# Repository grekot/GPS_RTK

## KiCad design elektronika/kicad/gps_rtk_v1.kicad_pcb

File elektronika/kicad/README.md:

# KiCad — schemat odbiornika GPS RTK (v1)

`gps_rtk_v1.kicad_sch` to **pełny schemat** z prawdziwymi symbolami KiCad i połączeniami
(po nazwach netów). Wygenerowany skryptem [gen/gen_schematic.py](gen/gen_schematic.py) z bibliotek
symboli KiCad 9, **zweryfikowany netlistą** i wyrenderowany do
[gps_rtk_v1.pdf](gps_rtk_v1.pdf) / [gps_rtk_v1.svg](gps_rtk_v1.svg).

## Zawartość schematu

Symbole: **U1** ESP32-WROOM-32; złącza modułów: **J1** GNSS LC29HEA, **J2** OLED SSD1306,
**J3** IMU BNO085 (v2, DNP), **J4** buck-boost 3V3, **J5** TP4056 USB-C; **BT1** ogniwo 18650;
dzielnik baterii **R1/R2** (100k); pull-upy I2C **R3/R4** (4k7); **R5**+**D1** LED statusu;
**SW1** przycisk; **C1/C2** bulk/odsprzęganie.

Nety (zweryfikowane netlistą): `+3V3, GND, VBAT, VBAT_SENSE, BATT_CELL, VBUS, GNSS_TX, GNSS_RX,
GNSS_PPS, GNSS_RST, SDA, SCL, LED_STAT, LED_A, BTN`. Zgodne z [../docs/05-pinout-firmware.md](../docs/05-pinout-firmware.md)
i [../docs/02-schemat-polaczen.md](../docs/02-schemat-polaczen.md).

> **Styl:** połączenia przez **etykiety netów po nazwie** (a nie rysowane przewody między częściami) —
> typowe i czytelne przy gęstych wyprowadzeniach MCU. Moduły jako złącza — w v1 to i tak gotowe
> płytki łączone przewodami. 24 nieużywane GPIO ESP32 zostają wolne (zapas).

## PCB — carrier `gps_rtk_v1.kicad_pcb`

**Płytka-baza (carrier) 100 × 78 mm**: wszystkie elementy aktywne to **gotowe moduły wpinane
w gniazda żeńskie** (łącznie z ESP32 jako devkit). Wygenerowana [gen/gen_pcb.py](gen/gen_pcb.py)
(pcbnew — Python KiCada). Podgląd: **[render 3D PNG](gps_rtk_v1_pcb.png)**, [2D SVG](gps_rtk_v1_pcb.svg).

Gniazda **PinSocket 2.54 mm**: **U1L+U1R** = ESP32 **DOIT DevKit V1 (30-pin)**, 2× **1×15**;
**J1** GNSS LC29HEA (1×06), **J2** OLED (1×04), **J3** IMU v2 (1×04), **J4** buck-boost (1×04),
**J5** TP4056 (1×06), **BT1** ogniwo (1×02). Na carrierze (SMD/THT): dzielnik **R1/R2**,
pull-upy I2C **R3/R4**, **R5+D1** LED, **C1/C2** bulk/odsprzęg., **SW1** przycisk.

**ESP32 jako devkit:** 3.3 V wchodzi na pin **3V3**; **EN i VIN(5V) wolne** — devkit ma własny
auto-reset i LDO (podpięcie EN do 3V3 zablokowałoby programowanie!). (Schemat pokazuje ESP32 jako
symbol WROOM — logicznie równoważny; na płytce to gniazdo devkitu.)

> **Zasilanie v1 = powerbank przez USB devkitu** (decyzja użytkownika). W tym trybie **nie montuj**
> modułów zasilania: buck-boost (J4), TP4056 (J5), ogniwo (BT1) ani dzielnika baterii (R1/R2) — szynę
> **+3V3** napędza wtedy AMS1117 devkitu. Sekcja bateryjna zostaje na płytce jako **opcja terenowa/v2**.

### Pinout ESP32 użyty na płytce — ZWERYFIKUJ z nadrukiem swojej płytki!

Kolejność fizyczna góra→dół (DOIT DevKit V1 30-pin). **Pogrubione = podłączone (mają net):**

| U1L (lewa) | net | · | U1R (prawa) | net |
|---|---|---|---|---|
| 1 EN | — | · | 1 3V3 | **+3V3** |
| 2 IO36 | — | · | 2 GND | **GND** |
| 3 IO39 | — | · | 3 IO15 | — |
| **4 IO34** | **VBAT_SENSE** | · | **4 IO2** | **LED_STAT** |
| **5 IO35** | **GNSS_PPS** | · | **5 IO4** | **GNSS_RST** |
| 6 IO32 | — | · | **6 IO16** | **GNSS_TX** |
| 7 IO33 | — | · | **7 IO17** | **GNSS_RX** |
| 8 IO25 | — | · | 8 IO5 | — |
| 9 IO26 | — | · | 9 IO18 | — |
| **10 IO27** | **BTN** | · | 10 IO19 | — |
| 11 IO14 | — | · | **11 IO21** | **SDA** |
| 12 IO12 | — | · | 12 IO3 | — |
| 13 IO13 | — | · | 13 IO1 | — |
| **14 GND** | **GND** | · | **14 IO22** | **SCL** |
| 15 VIN | — | · | 15 IO23 | — |

**Stan: rozmieszczona + onetowana, NIETRASOWANA** (ratsnest). DRC: **0 naruszeń**, 0 błędów
footprintów; **43 pady do połączenia = trasowanie**.

> ⚠️ **Zweryfikuj pod swój egzemplarz:** (1) **rozstaw rzędów** gniazd ESP32 — przyjąłem **22,86 mm**
> (stała `ESP_ROW_MM` w [gen/gen_pcb.py](gen/gen_pcb.py)); zmierz środek-do-środka rzędów i popraw.
> (2) **Pinout** wg tabeli wyżej — klony 30-pin bywają różne; jeśli się różni, popraw listy
> `ESP_L`/`ESP_R`. Rozmieszczenie zgrubne — dociągnij w GUI pod krótkie trasy.

## Weryfikacja (bez ERC — patrz niżej)

- ✅ **Netlista** (`kicad-cli sch export netlist`) — przeszła; każdy net ma dokładnie właściwe węzły
  (sprawdzone programowo: brak zlanych/rozjechanych netów).
- ✅ **Render** PDF/SVG (`kicad-cli sch export`) — bez błędów (10935 elementów rysunku).
- ⚠️ `kicad-cli sch erc` **crashuje** na tym pliku (quirk zgodności wyjścia generatora `kiutils`
  z silnikiem ERC w kicad-cli 9.0.9). Dlatego poprawność połączeń potwierdziłem **netlistą**, nie ERC.
  Po otwarciu i zapisaniu pliku w **GUI KiCada** (które normalizuje format) ERC powinien działać.

## Dalej (trasowanie + produkcja)

- **Trasowanie ścieżek** — jedyny brakujący krok: w GUI pcbnew, albo autorouterem **freerouting**
  (eksport `.dsn` → route → import `.ses`). Warto **wylać masę (GND pour)** — skróci ratsnest.
- Po trasowaniu: DRC w GUI, **gerbery** (`kicad-cli pcb export gerbers`), plik wierceń, BOM/CPL.
- Sekcja RF/bias anteny dla gołego modułu — patrz [../docs/02-schemat-polaczen.md](../docs/02-schemat-polaczen.md).

## Regeneracja / eksport

```powershell
$cli = "C:\TMP\kicad_portable\bin\kicad-cli.exe"   # lub kicad-cli z instalacji
py -3 gen\gen_schematic.py                          # wymaga: pip install kiutils
& $cli sch export pdf     --output gps_rtk_v1.pdf gps_rtk_v1.kicad_sch
& $cli sch export svg     --output .               gps_rtk_v1.kicad_sch
& $cli sch export netlist --output gps_rtk_v1.net  gps_rtk_v1.kicad_sch
# PCB (pcbnew — Python KiCada):
& "C:\TMP\kicad_portable\bin\python.exe" gen\gen_pcb.py
& $cli pcb drc    --output pcb.drc.rpt        gps_rtk_v1.kicad_pcb
& $cli pcb render --output gps_rtk_v1_pcb.png gps_rtk_v1.kicad_pcb
```

## Portable KiCad (rozpakowany w tej sesji)

Instalator rozpakowano 7-Zipem **bez instalacji i bez praw admina** do `C:\TMP\kicad_portable\`.
Działa GUI (`bin\kicad.exe`) i CLI (`bin\kicad-cli.exe`). Otwórz schemat:
`& "C:\TMP\kicad_portable\bin\kicad.exe" "...\elektronika\kicad\gps_rtk_v1.kicad_pro"`.
Folder można usunąć (~kilka GB) albo zachować jako przenośny KiCad.

## Instalacja KiCada na stałe (brak winget w systemie)

1. **Bezpośrednio:** <https://www.kicad.org/download/windows/> (KiCad 9/10).
2. **winget** (po doinstalowaniu „App Installer" z MS Store): `winget install -e --id KiCad.KiCad`.
3. **Chocolatey:** `choco install kicad`.

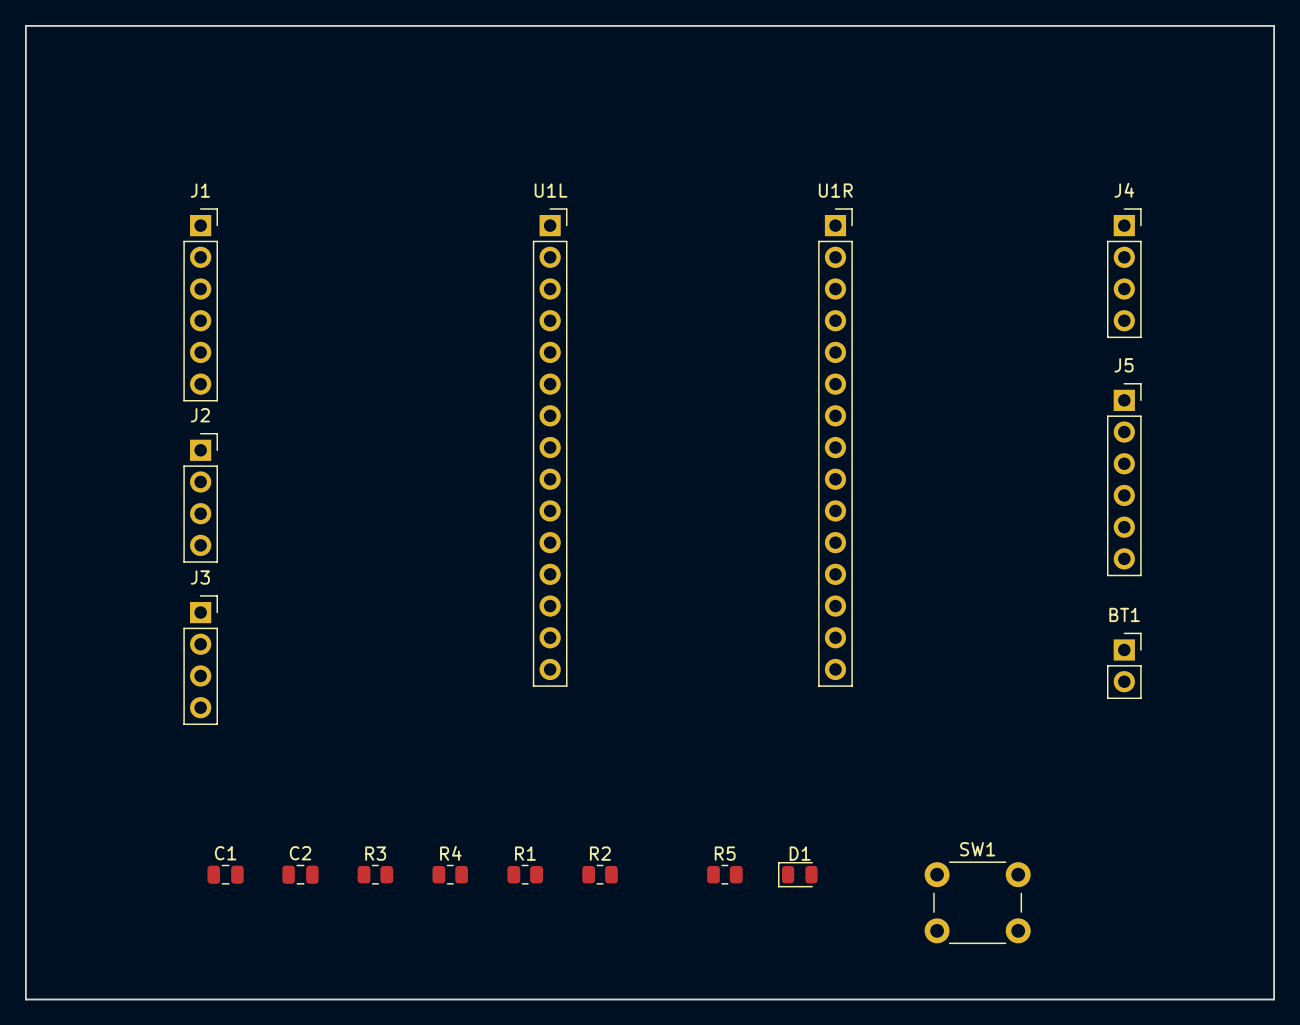
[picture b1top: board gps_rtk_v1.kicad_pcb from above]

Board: 2 copper layers, 100.0 x 78.0 mm, 17 parts (0 on the bottom side), 14 nets, no tracks yet.

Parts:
BT1: 18650 (przewody); PinSocket_1x02_P2.54mm_Vertical
C1: 100uF; C_0805_2012Metric
C2: 100nF; C_0805_2012Metric
D1: status; LED_0805_2012Metric
J1: GNSS LC29HEA (modul); PinSocket_1x06_P2.54mm_Vertical
J2: OLED SSD1306 (modul); PinSocket_1x04_P2.54mm_Vertical
J3: IMU BNO085 v2 (modul); PinSocket_1x04_P2.54mm_Vertical
J4: Buck-boost 3V3 (modul); PinSocket_1x04_P2.54mm_Vertical
J5: TP4056 USB-C (modul); PinSocket_1x06_P2.54mm_Vertical
R1, R2: 100k; R_0805_2012Metric
R3, R4: 4k7; R_0805_2012Metric
R5: 330; R_0805_2012Metric
SW1: user; SW_PUSH_6mm_H5mm
U1L: ESP32 DevKit V1 (L); PinSocket_1x15_P2.54mm_Vertical
U1R: ESP32 DevKit V1 (R); PinSocket_1x15_P2.54mm_Vertical

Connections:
+3V3: C1.1, C2.1, J1.1, J2.1, J3.1, J4.3, J4.4, R3.1, R4.1, U1R.1
BATT_CELL: BT1.1, J5.3
BTN: SW1.1, U1L.10
GND: BT1.2, C1.2, C2.2, D1.1, J1.2, J2.2, J3.2, J4.2, J5.2, J5.4, J5.6, R2.2, SW1.2, U1L.14, U1R.2
GNSS_PPS: J1.5, U1L.5
GNSS_RST: J1.6, U1R.5
GNSS_RX: J1.4, U1R.7
GNSS_TX: J1.3, U1R.6
LED_A: D1.2, R5.2
LED_STAT: R5.1, U1R.4
SCL: J2.3, J3.3, R4.2, U1R.14
SDA: J2.4, J3.4, R3.2, U1R.11
VBAT: J4.1, J5.5, R1.1
VBAT_SENSE: R1.2, R2.1, U1L.4

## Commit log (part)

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2026-06-29 Aplikacja Flutter GPS RTK + CI (build APK na GitHub Actions)
